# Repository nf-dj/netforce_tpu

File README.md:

Netforce TPU
============

Building hardware to run transformer neural networks at low cost.

Join the [Discord server](https://discord.gg/e4aWKnZZ) for questions and discussions.

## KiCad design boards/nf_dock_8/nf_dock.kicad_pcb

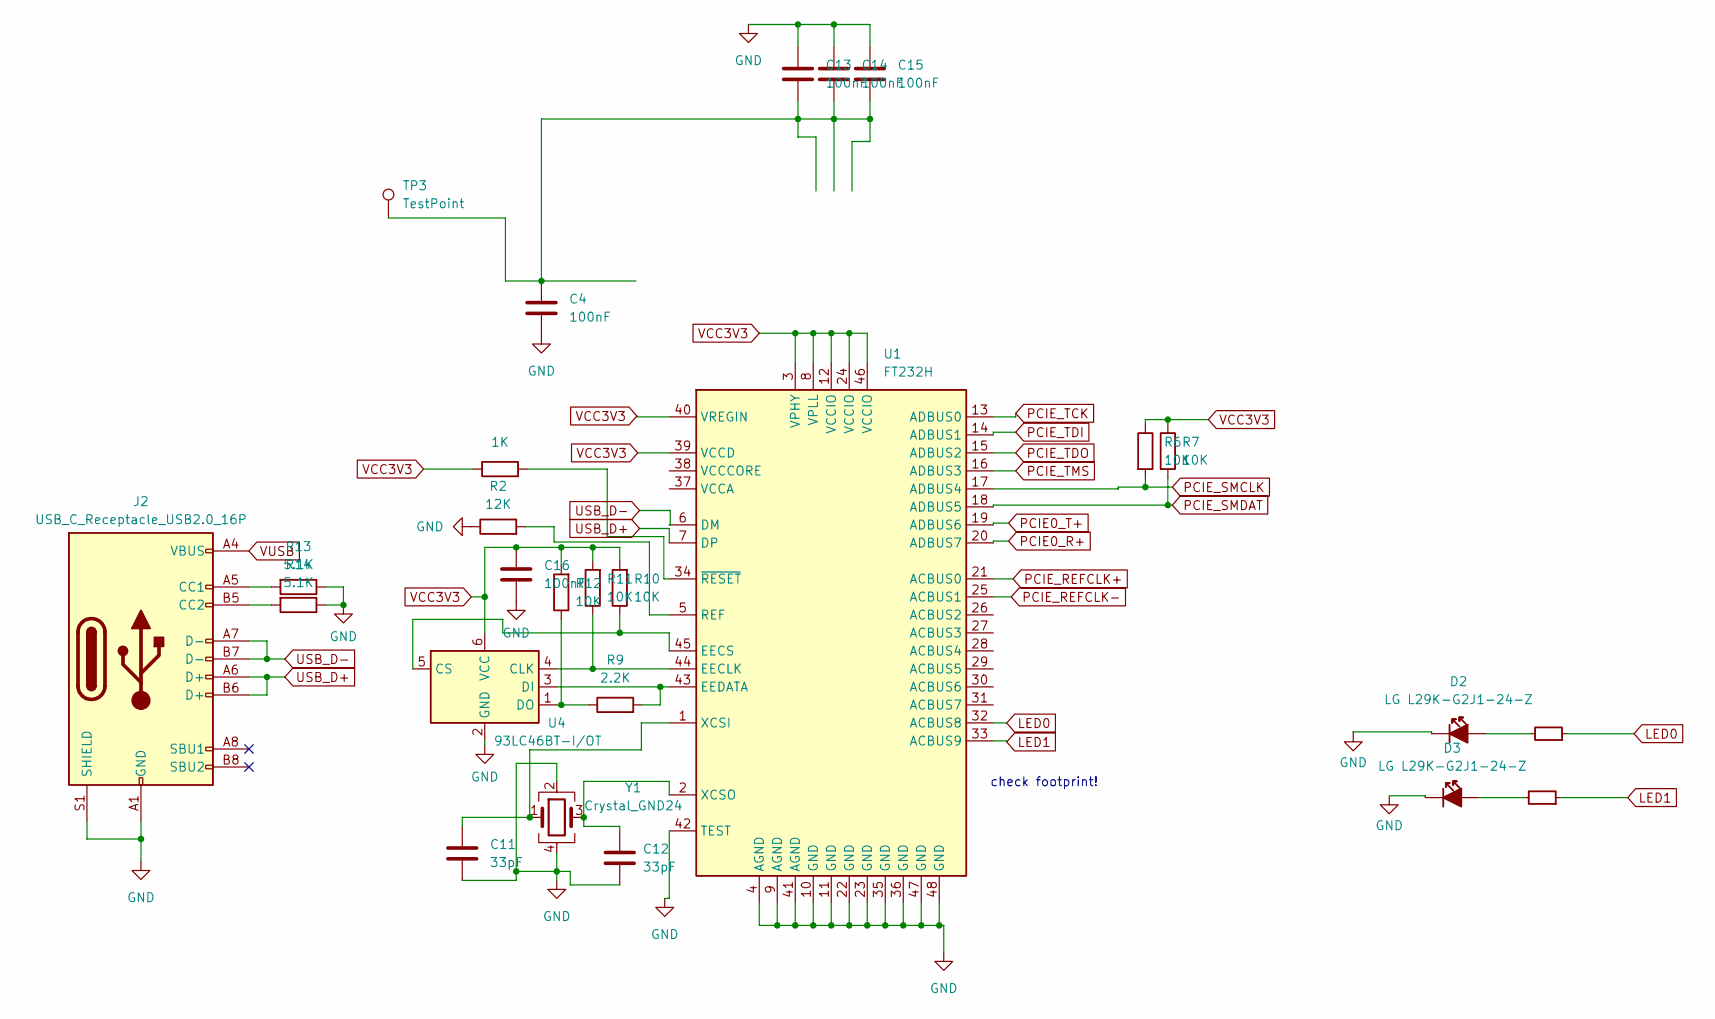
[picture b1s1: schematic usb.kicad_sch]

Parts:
C4, C13, C14, C15, C16: 100nF; C_0402_1005Metric; LCSC C1525
C11, C12: 33pF; C_0402_1005Metric; LCSC C1562
D2: LED_G_0603_LG_L29K-G2J1-24-Z; LED_0805_2012Metric; MPN LG L29K-G2J1-24-Z; LCSC C2297
D3: LED_G_0603_LG_L29K-G2J1-24-Z; LED_0805_2012Metric; MPN LG L29K-G2J1-24-Z; LCSC C84256
J2: USB_C_Receptacle_USB2.0_16P; USB_C_Receptacle_XKB_U262-16XN-4BVC11; LCSC C165948
R2: 12K; R_0402_1005Metric; LCSC C25752
R6, R7, R10, R11, R12: 10K; R_0402_1005Metric; LCSC C25744
R8: 1K; R_0402_1005Metric; LCSC C11702
R9: 2.2K; R_0402_1005Metric; LCSC C25879
R13, R14: 5.1K; R_0402_1005Metric; LCSC C25905
R16, R17: 330R; R_0402_1005Metric; Tolerance 1%; MPN CR0402-FX-1001GLF; LCSC C25104
TP3: TestPoint; TestPoint_Pad_D1.0mm
U1: FT232H; QFN-48-1EP_7x7mm_P0.5mm_EP3.5x3.5mm; LCSC C51997
U4: 93LC46BT-I/OT; SOT-23-6; LCSC C190271
Y1: Crystal_GND24; Crystal_SMD_3225-4Pin_3.2x2.5mm; LCSC C9002

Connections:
GND: C4.2, C11.2, C12.2, C13.1, C14.1, C15.1, C16.2, D2.2, D3.2, J2.A1 (GND), J2.A12 (GND), J2.B1 (GND), J2.B12 (GND), J2.S1 (SHIELD), R2.1, R13.1, R14.1, U1.4 (AGND), U1.9 (AGND), U1.10 (GND), U1.11 (GND), U1.22 (GND), U1.23 (GND), U1.35 (GND), U1.36 (GND), U1.42 (TEST), U1.47 (GND), U1.48 (GND), U4.2 (GND), Y1.2, Y1.4; also elsewhere on the board
LED0: R17.1, U1.32 (ACBUS8)
LED1: R16.1, U1.33 (ACBUS9)
unnamed: C4.1, C13.2, C14.2, C15.2, TP3.1
unnamed: D2.1, R17.2
unnamed: D3.1, R16.2
unnamed: J2.A5 (CC1), R13.2
unnamed: J2.B5 (CC2), R14.2
unnamed: R11.1, U1.44 (EECLK), U4.4 (CLK)
unnamed: R10.1, U1.45 (EECS), U4.5 (CS)
unnamed: R9.2, U1.43 (EEDATA), U4.3 (DI)
unnamed: R2.2, U1.5 (REF)
unnamed: C11.1, U1.1 (XCSI), Y1.1
unnamed: C12.1, U1.2 (XCSO), Y1.3
unnamed: R8.2, U1.34 (~RESET)
unnamed: R9.1, R12.1, U4.1 (DO)
PCIE0_R+: U1.20 (ADBUS7); also elsewhere on the board
PCIE0_T+: U1.19 (ADBUS6); also elsewhere on the board
PCIE_REFCLK+: U1.21 (ACBUS0); also elsewhere on the board
PCIE_REFCLK-: U1.25 (ACBUS1); also elsewhere on the board
PCIE_SMCLK: R6.2, U1.17 (ADBUS4); also elsewhere on the board
PCIE_SMDAT: R7.2, U1.18 (ADBUS5); also elsewhere on the board
PCIE_TCK: U1.13 (ADBUS0); also elsewhere on the board
PCIE_TDI: U1.14 (ADBUS1); also elsewhere on the board
PCIE_TDO: U1.15 (ADBUS2); also elsewhere on the board
PCIE_TMS: U1.16 (ADBUS3); also elsewhere on the board
USB_D+: J2.A6 (D+), J2.B6 (D+), U1.7 (DP)
USB_D-: J2.A7 (D-), J2.B7 (D-), U1.6 (DM)
VCC3V3: C16.1, R6.1, R7.1, R8.1, R10.2, R11.2, R12.2, U1.3 (VPHY), U1.8 (VPLL), U1.12 (VCCIO), U1.24 (VCCIO), U1.39 (VCCD), U1.40 (VREGIN), U1.46 (VCCIO), U4.6 (VCC); also elsewhere on the board
VUSB: J2.A4 (VBUS), J2.A9 (VBUS), J2.B4 (VBUS), J2.B9 (VBUS); also elsewhere on the board

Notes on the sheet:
check footprint!

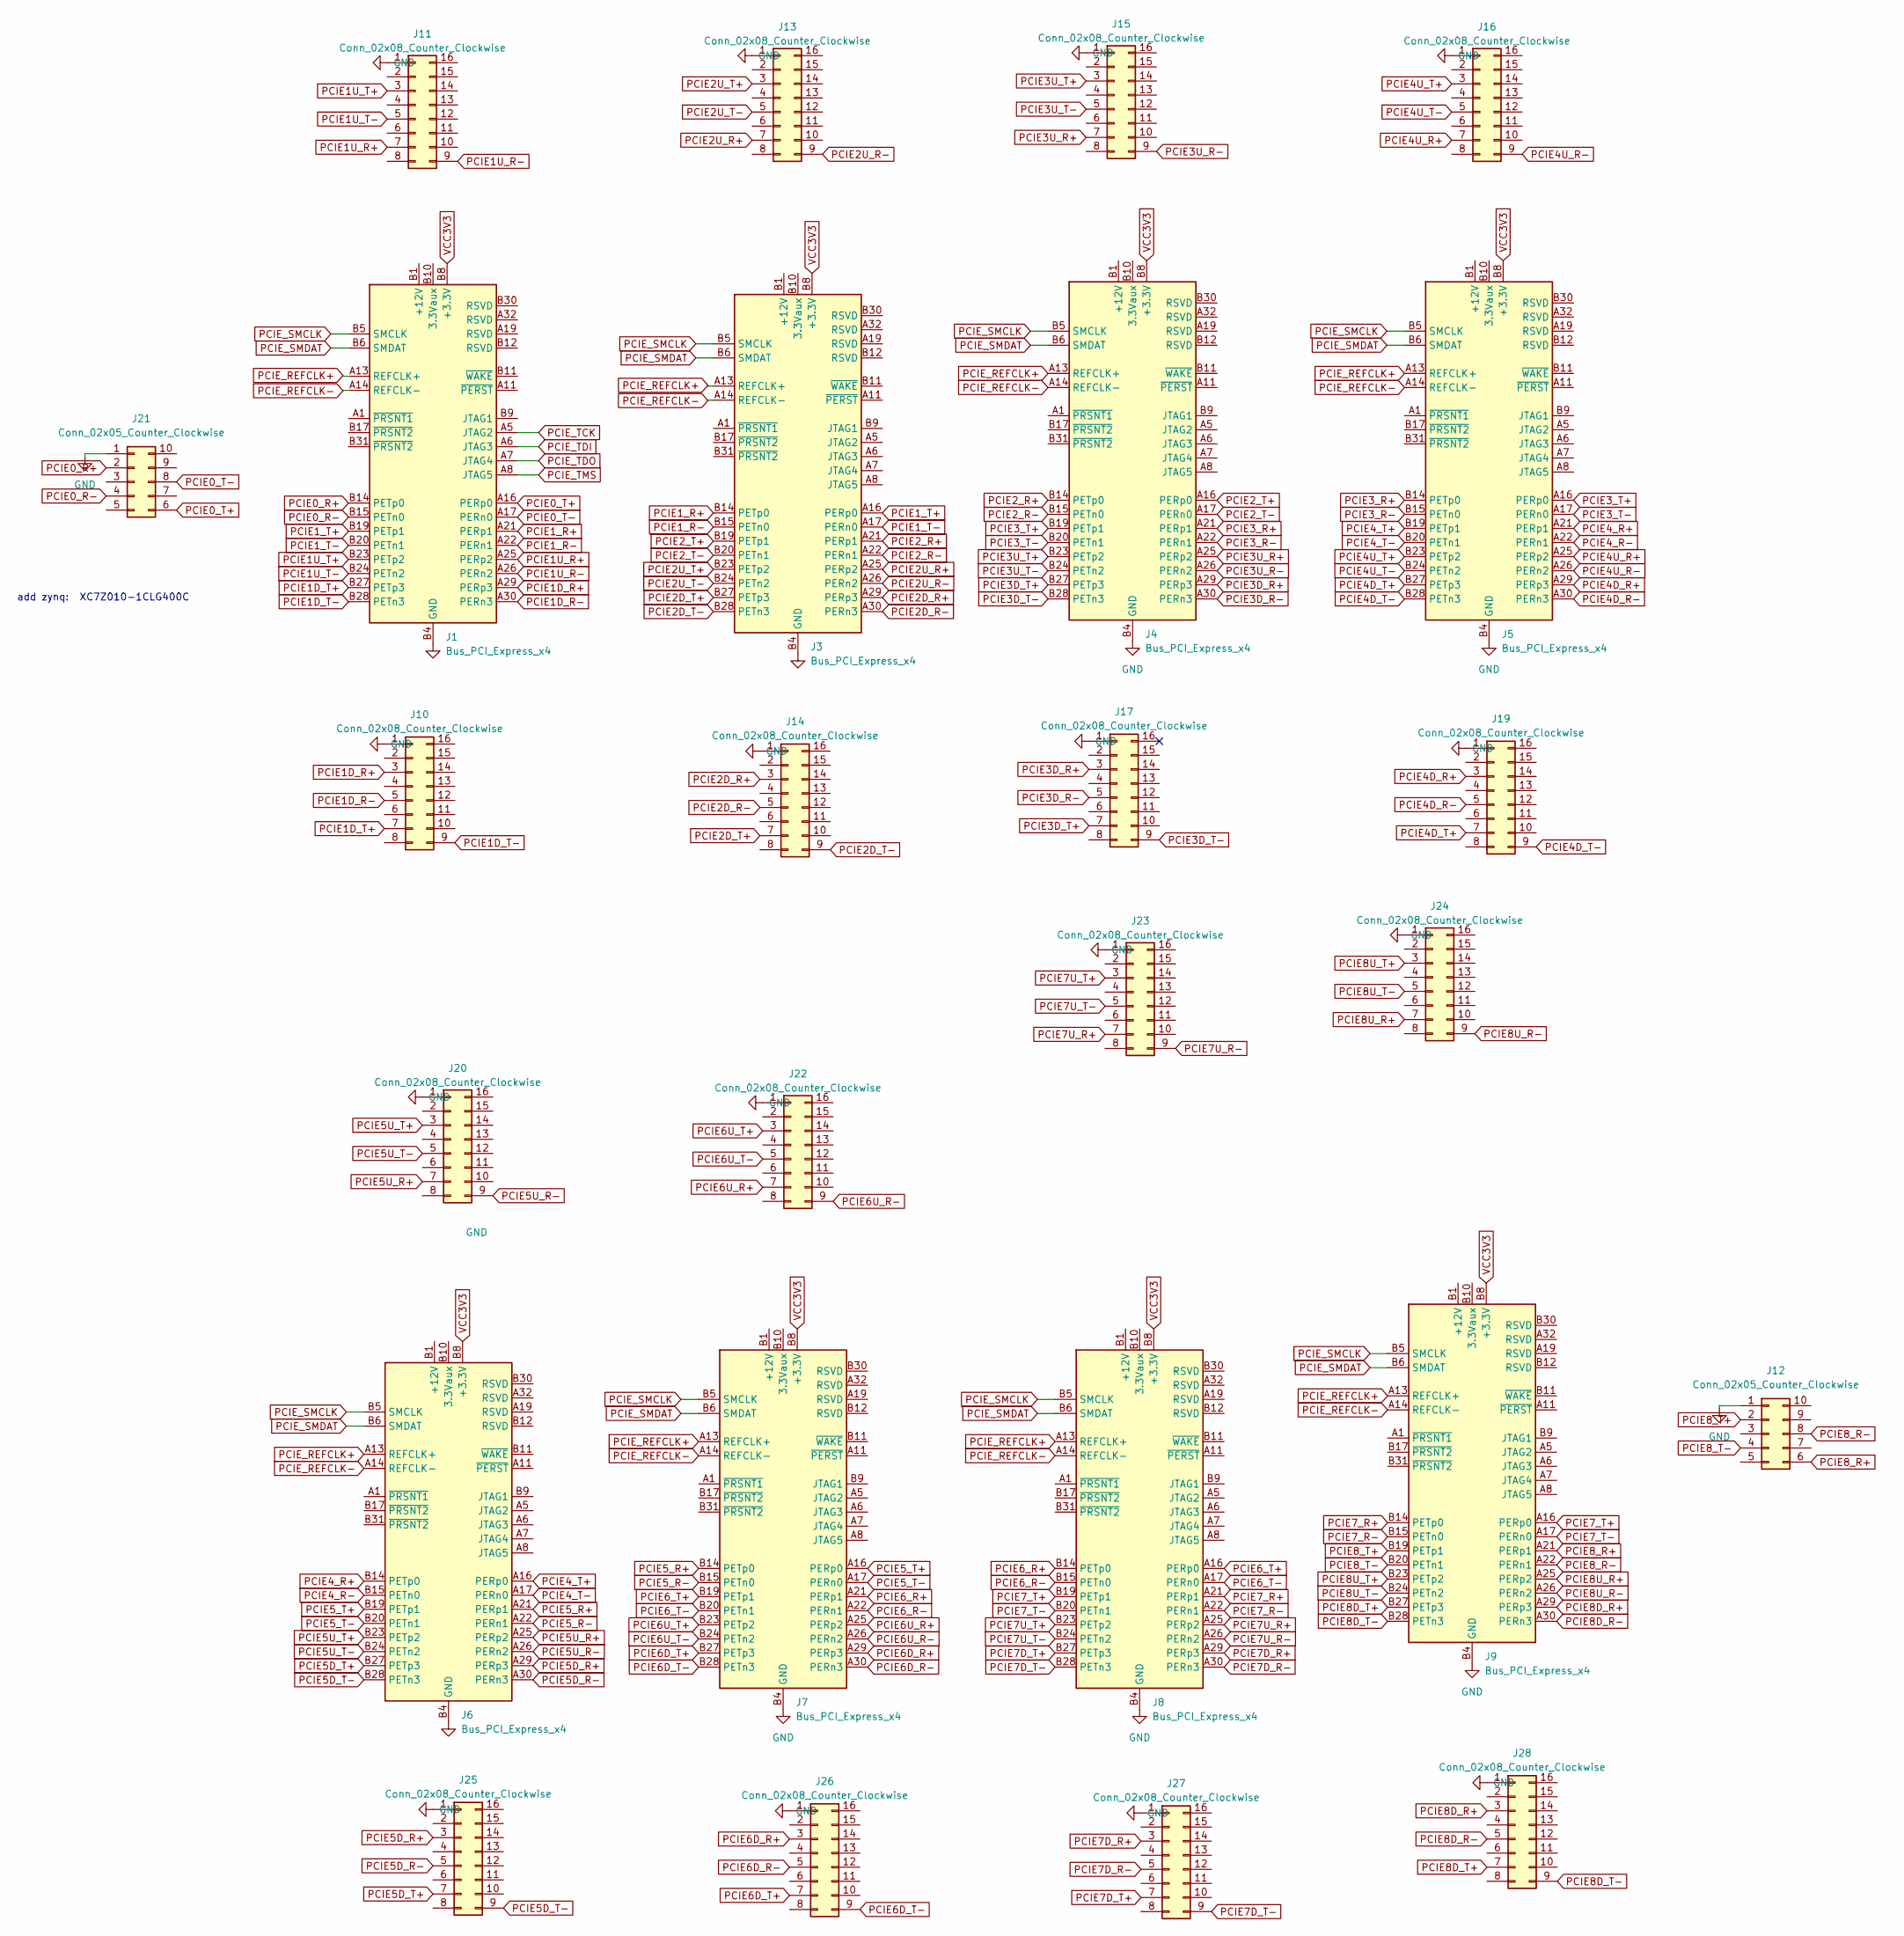
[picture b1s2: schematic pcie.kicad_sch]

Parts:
J1, J3, J4, J5, J6, J7, J8, J9: Bus_PCI_Express_x4; pcie-x4-slot; LCSC C404102
J10, J14, J17, J19, J25, J26, J27, J28: Conn_02x08_Counter_Clockwise; PinSocket_2x08_P1.27mm_Horizontal
J11, J13, J15, J16, J20, J22, J23, J24: Conn_02x08_Counter_Clockwise; PinHeader_2x08_P1.27mm_Horizontal; LCSC C2881828
J12, J21: Conn_02x05_Counter_Clockwise; IDC-Header_2x05_P2.54mm_Vertical

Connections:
GND: J1.A4 (GND), J1.A12 (GND), J1.A15 (GND), J1.A18 (GND), J1.A20 (GND), J1.A23 (GND), J1.A24 (GND), J1.A27 (GND), J1.A28 (GND), J1.A31 (GND), J1.B4 (GND), J1.B7 (GND), J1.B13 (GND), J1.B16 (GND), J1.B18 (GND), J1.B21 (GND), J1.B22 (GND), J1.B25 (GND), J1.B26 (GND), J1.B29 (GND), J1.B32 (GND), J3.A4 (GND), J3.A12 (GND), J3.A15 (GND), J3.A18 (GND), J3.A20 (GND), J3.A23 (GND), J3.A24 (GND), J3.A27 (GND), J3.A28 (GND), J3.A31 (GND), J3.B4 (GND), J3.B7 (GND), J3.B13 (GND), J3.B16 (GND), J3.B18 (GND), J3.B21 (GND), J3.B22 (GND), J3.B25 (GND), J3.B26 (GND), J3.B29 (GND), J3.B32 (GND), J4.A4 (GND), J4.A12 (GND), J4.A15 (GND), J4.A18 (GND), J4.A20 (GND), J4.A23 (GND), J4.A24 (GND), J4.A27 (GND), J4.A28 (GND), J4.A31 (GND), J4.B4 (GND), J4.B7 (GND), J4.B13 (GND), J4.B16 (GND), J4.B18 (GND), J4.B21 (GND), J4.B22 (GND), J4.B25 (GND), J4.B26 (GND), J4.B29 (GND), J4.B32 (GND), J5.A4 (GND), J5.A12 (GND), J5.A15 (GND), J5.A18 (GND), J5.A20 (GND), J5.A23 (GND), J5.A24 (GND), J5.A27 (GND), J5.A28 (GND), J5.A31 (GND), J5.B4 (GND), J5.B7 (GND), J5.B13 (GND), J5.B16 (GND), J5.B18 (GND), J5.B21 (GND), J5.B22 (GND), J5.B25 (GND), J5.B26 (GND), J5.B29 (GND), J5.B32 (GND), J6.A4 (GND), J6.A12 (GND), J6.A15 (GND), J6.A18 (GND), J6.A20 (GND), J6.A23 (GND), J6.A24 (GND), J6.A27 (GND), J6.A28 (GND), J6.A31 (GND), J6.B4 (GND), J6.B7 (GND), J6.B13 (GND), J6.B16 (GND), J6.B18 (GND), J6.B21 (GND), J6.B22 (GND), J6.B25 (GND), J6.B26 (GND), J6.B29 (GND), J6.B32 (GND), J7.A4 (GND), J7.A12 (GND), J7.A15 (GND), J7.A18 (GND), J7.A20 (GND), J7.A23 (GND), J7.A24 (GND), J7.A27 (GND), J7.A28 (GND), J7.A31 (GND), J7.B4 (GND), J7.B7 (GND), J7.B13 (GND), J7.B16 (GND), J7.B18 (GND), J7.B21 (GND), J7.B22 (GND), J7.B25 (GND), J7.B26 (GND), J7.B29 (GND), J7.B32 (GND), J8.A4 (GND), J8.A12 (GND), J8.A15 (GND), J8.A18 (GND), J8.A20 (GND), J8.A23 (GND), J8.A24 (GND), J8.A27 (GND), J8.A28 (GND), J8.A31 (GND), J8.B4 (GND), J8.B7 (GND), J8.B13 (GND), J8.B16 (GND), J8.B18 (GND), J8.B21 (GND), J8.B22 (GND), J8.B25 (GND), J8.B26 (GND), J8.B29 (GND), J8.B32 (GND), J9.A4 (GND), J9.A12 (GND), J9.A15 (GND), J9.A18 (GND), J9.A20 (GND), J9.A23 (GND), J9.A24 (GND), J9.A27 (GND), J9.A28 (GND), J9.A31 (GND), J9.B4 (GND), J9.B7 (GND), J9.B13 (GND), J9.B16 (GND), J9.B18 (GND), J9.B21 (GND), J9.B22 (GND), J9.B25 (GND), J9.B26 (GND), J9.B29 (GND), J9.B32 (GND), J10.1, J11.1, J12.1, J13.1, J14.1, J15.1, J16.1, J17.1, J19.1, J20.1, J21.1, J22.1, J23.1, J24.1, J25.1, J26.1, J27.1, J28.1; also elsewhere on the board
unnamed: J1.A2 (+12V), J1.A3 (+12V), J1.B1 (+12V), J1.B2 (+12V), J1.B3 (+12V)
unnamed: J3.A2 (+12V), J3.A3 (+12V), J3.B1 (+12V), J3.B2 (+12V), J3.B3 (+12V)
unnamed: J4.A2 (+12V), J4.A3 (+12V), J4.B1 (+12V), J4.B2 (+12V), J4.B3 (+12V)
unnamed: J5.A2 (+12V), J5.A3 (+12V), J5.B1 (+12V), J5.B2 (+12V), J5.B3 (+12V)
unnamed: J6.A2 (+12V), J6.A3 (+12V), J6.B1 (+12V), J6.B2 (+12V), J6.B3 (+12V)
unnamed: J7.A2 (+12V), J7.A3 (+12V), J7.B1 (+12V), J7.B2 (+12V), J7.B3 (+12V)
unnamed: J8.A2 (+12V), J8.A3 (+12V), J8.B1 (+12V), J8.B2 (+12V), J8.B3 (+12V)
unnamed: J9.A2 (+12V), J9.A3 (+12V), J9.B1 (+12V), J9.B2 (+12V), J9.B3 (+12V)
PCIE0_R+: J1.B14 (PETp0), J21.2; also elsewhere on the board
PCIE0_R-: J1.B15 (PETn0), J21.4
PCIE0_T+: J1.A16 (PERp0), J21.6; also elsewhere on the board
PCIE0_T-: J1.A17 (PERn0), J21.8
PCIE1D_R+: J1.A29 (PERp3), J10.3
PCIE1D_R-: J1.A30 (PERn3), J10.5
PCIE1D_T+: J1.B27 (PETp3), J10.7
PCIE1D_T-: J1.B28 (PETn3), J10.9
PCIE1U_R+: J1.A25 (PERp2), J11.7
PCIE1U_R-: J1.A26 (PERn2), J11.9
PCIE1U_T+: J1.B23 (PETp2), J11.3
PCIE1U_T-: J1.B24 (PETn2), J11.5
PCIE1_R+: J1.A21 (PERp1), J3.B14 (PETp0)
PCIE1_R-: J1.A22 (PERn1), J3.B15 (PETn0)
PCIE1_T+: J1.B19 (PETp1), J3.A16 (PERp0)
PCIE1_T-: J1.B20 (PETn1), J3.A17 (PERn0)
PCIE2D_R+: J3.A29 (PERp3), J14.3
PCIE2D_R-: J3.A30 (PERn3), J14.5
PCIE2D_T+: J3.B27 (PETp3), J14.7
PCIE2D_T-: J3.B28 (PETn3), J14.9
PCIE2U_R+: J3.A25 (PERp2), J13.7
PCIE2U_R-: J3.A26 (PERn2), J13.9
PCIE2U_T+: J3.B23 (PETp2), J13.3
PCIE2U_T-: J3.B24 (PETn2), J13.5
PCIE2_R+: J3.A21 (PERp1), J4.B14 (PETp0)
PCIE2_R-: J3.A22 (PERn1), J4.B15 (PETn0)
PCIE2_T+: J3.B19 (PETp1), J4.A16 (PERp0)
PCIE2_T-: J3.B20 (PETn1), J4.A17 (PERn0)
PCIE3D_R+: J4.A29 (PERp3), J17.3
PCIE3D_R-: J4.A30 (PERn3), J17.5
PCIE3D_T+: J4.B27 (PETp3), J17.7
PCIE3D_T-: J4.B28 (PETn3), J17.9
PCIE3U_R+: J4.A25 (PERp2), J15.7
PCIE3U_R-: J4.A26 (PERn2), J15.9
PCIE3U_T+: J4.B23 (PETp2), J15.3
PCIE3U_T-: J4.B24 (PETn2), J15.5
PCIE3_R+: J4.A21 (PERp1), J5.B14 (PETp0)
PCIE3_R-: J4.A22 (PERn1), J5.B15 (PETn0)
PCIE3_T+: J4.B19 (PETp1), J5.A16 (PERp0)
PCIE3_T-: J4.B20 (PETn1), J5.A17 (PERn0)
PCIE4D_R+: J5.A29 (PERp3), J19.3
PCIE4D_R-: J5.A30 (PERn3), J19.5
PCIE4D_T+: J5.B27 (PETp3), J19.7
PCIE4D_T-: J5.B28 (PETn3), J19.9
PCIE4U_R+: J5.A25 (PERp2), J16.7
PCIE4U_R-: J5.A26 (PERn2), J16.9
PCIE4U_T+: J5.B23 (PETp2), J16.3
PCIE4U_T-: J5.B24 (PETn2), J16.5
PCIE4_R+: J5.A21 (PERp1), J6.B14 (PETp0)
PCIE4_R-: J5.A22 (PERn1), J6.B15 (PETn0)
PCIE4_T+: J5.B19 (PETp1), J6.A16 (PERp0)
PCIE4_T-: J5.B20 (PETn1), J6.A17 (PERn0)
PCIE5D_R+: J6.A29 (PERp3), J25.3
PCIE5D_R-: J6.A30 (PERn3), J25.5
PCIE5D_T+: J6.B27 (PETp3), J25.7
PCIE5D_T-: J6.B28 (PETn3), J25.9
PCIE5U_R+: J6.A25 (PERp2), J20.7
PCIE5U_R-: J6.A26 (PERn2), J20.9
PCIE5U_T+: J6.B23 (PETp2), J20.3
PCIE5U_T-: J6.B24 (PETn2), J20.5
PCIE5_R+: J6.A21 (PERp1), J7.B14 (PETp0)
PCIE5_R-: J6.A22 (PERn1), J7.B15 (PETn0)
PCIE5_T+: J6.B19 (PETp1), J7.A16 (PERp0)
PCIE5_T-: J6.B20 (PETn1), J7.A17 (PERn0)
PCIE6D_R+: J7.A29 (PERp3), J26.3
PCIE6D_R-: J7.A30 (PERn3), J26.5
PCIE6D_T+: J7.B27 (PETp3), J26.7
PCIE6D_T-: J7.B28 (PETn3), J26.9
PCIE6U_R+: J7.A25 (PERp2), J22.7
PCIE6U_R-: J7.A26 (PERn2), J22.9
PCIE6U_T+: J7.B23 (PETp2), J22.3
PCIE6U_T-: J7.B24 (PETn2), J22.5
PCIE6_R+: J7.A21 (PERp1), J8.B14 (PETp0)
PCIE6_R-: J7.A22 (PERn1), J8.B15 (PETn0)
PCIE6_T+: J7.B19 (PETp1), J8.A16 (PERp0)
PCIE6_T-: J7.B20 (PETn1), J8.A17 (PERn0)
PCIE7D_R+: J8.A29 (PERp3), J27.3
PCIE7D_R-: J8.A30 (PERn3), J27.5
PCIE7D_T+: J8.B27 (PETp3), J27.7
PCIE7D_T-: J8.B28 (PETn3), J27.9
PCIE7U_R+: J8.A25 (PERp2), J23.7
PCIE7U_R-: J8.A26 (PERn2), J23.9
PCIE7U_T+: J8.B23 (PETp2), J23.3
PCIE7U_T-: J8.B24 (PETn2), J23.5
PCIE7_R+: J8.A21 (PERp1), J9.B14 (PETp0)
PCIE7_R-: J8.A22 (PERn1), J9.B15 (PETn0)
PCIE7_T+: J8.B19 (PETp1), J9.A16 (PERp0)
PCIE7_T-: J8.B20 (PETn1), J9.A17 (PERn0)
PCIE8D_R+: J9.A29 (PERp3), J28.3
PCIE8D_R-: J9.A30 (PERn3), J28.5
PCIE8D_T+: J9.B27 (PETp3), J28.7
PCIE8D_T-: J9.B28 (PETn3), J28.9
PCIE8U_R+: J9.A25 (PERp2), J24.7
PCIE8U_R-: J9.A26 (PERn2), J24.9
PCIE8U_T+: J9.B23 (PETp2), J24.3
PCIE8U_T-: J9.B24 (PETn2), J24.5
PCIE8_R+: J9.A21 (PERp1), J12.6
PCIE8_R-: J9.A22 (PERn1), J12.8
PCIE8_T+: J9.B19 (PETp1), J12.2
PCIE8_T-: J9.B20 (PETn1), J12.4
PCIE_REFCLK+: J1.A13 (REFCLK+), J3.A13 (REFCLK+), J4.A13 (REFCLK+), J5.A13 (REFCLK+), J6.A13 (REFCLK+), J7.A13 (REFCLK+), J8.A13 (REFCLK+), J9.A13 (REFCLK+); also elsewhere on the board
PCIE_REFCLK-: J1.A14 (REFCLK-), J3.A14 (REFCLK-), J4.A14 (REFCLK-), J5.A14 (REFCLK-), J6.A14 (REFCLK-), J7.A14 (REFCLK-), J8.A14 (REFCLK-), J9.A14 (REFCLK-); also elsewhere on the board
PCIE_SMCLK: J1.B5 (SMCLK), J3.B5 (SMCLK), J4.B5 (SMCLK), J5.B5 (SMCLK), J6.B5 (SMCLK), J7.B5 (SMCLK), J8.B5 (SMCLK), J9.B5 (SMCLK); also elsewhere on the board
PCIE_SMDAT: J1.B6 (SMDAT), J3.B6 (SMDAT), J4.B6 (SMDAT), J5.B6 (SMDAT), J6.B6 (SMDAT), J7.B6 (SMDAT), J8.B6 (SMDAT), J9.B6 (SMDAT); also elsewhere on the board
PCIE_TCK: J1.A5 (JTAG2); also elsewhere on the board
PCIE_TDI: J1.A6 (JTAG3); also elsewhere on the board
PCIE_TDO: J1.A7 (JTAG4); also elsewhere on the board
PCIE_TMS: J1.A8 (JTAG5); also elsewhere on the board
VCC3V3: J1.A9 (+3.3V), J1.A10 (+3.3V), J1.B8 (+3.3V), J3.A9 (+3.3V), J3.A10 (+3.3V), J3.B8 (+3.3V), J4.A9 (+3.3V), J4.A10 (+3.3V), J4.B8 (+3.3V), J5.A9 (+3.3V), J5.A10 (+3.3V), J5.B8 (+3.3V), J6.A9 (+3.3V), J6.A10 (+3.3V), J6.B8 (+3.3V), J7.A9 (+3.3V), J7.A10 (+3.3V), J7.B8 (+3.3V), J8.A9 (+3.3V), J8.A10 (+3.3V), J8.B8 (+3.3V), J9.A9 (+3.3V), J9.A10 (+3.3V), J9.B8 (+3.3V); also elsewhere on the board

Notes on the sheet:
add zynq: XC7Z010-1CLG400C

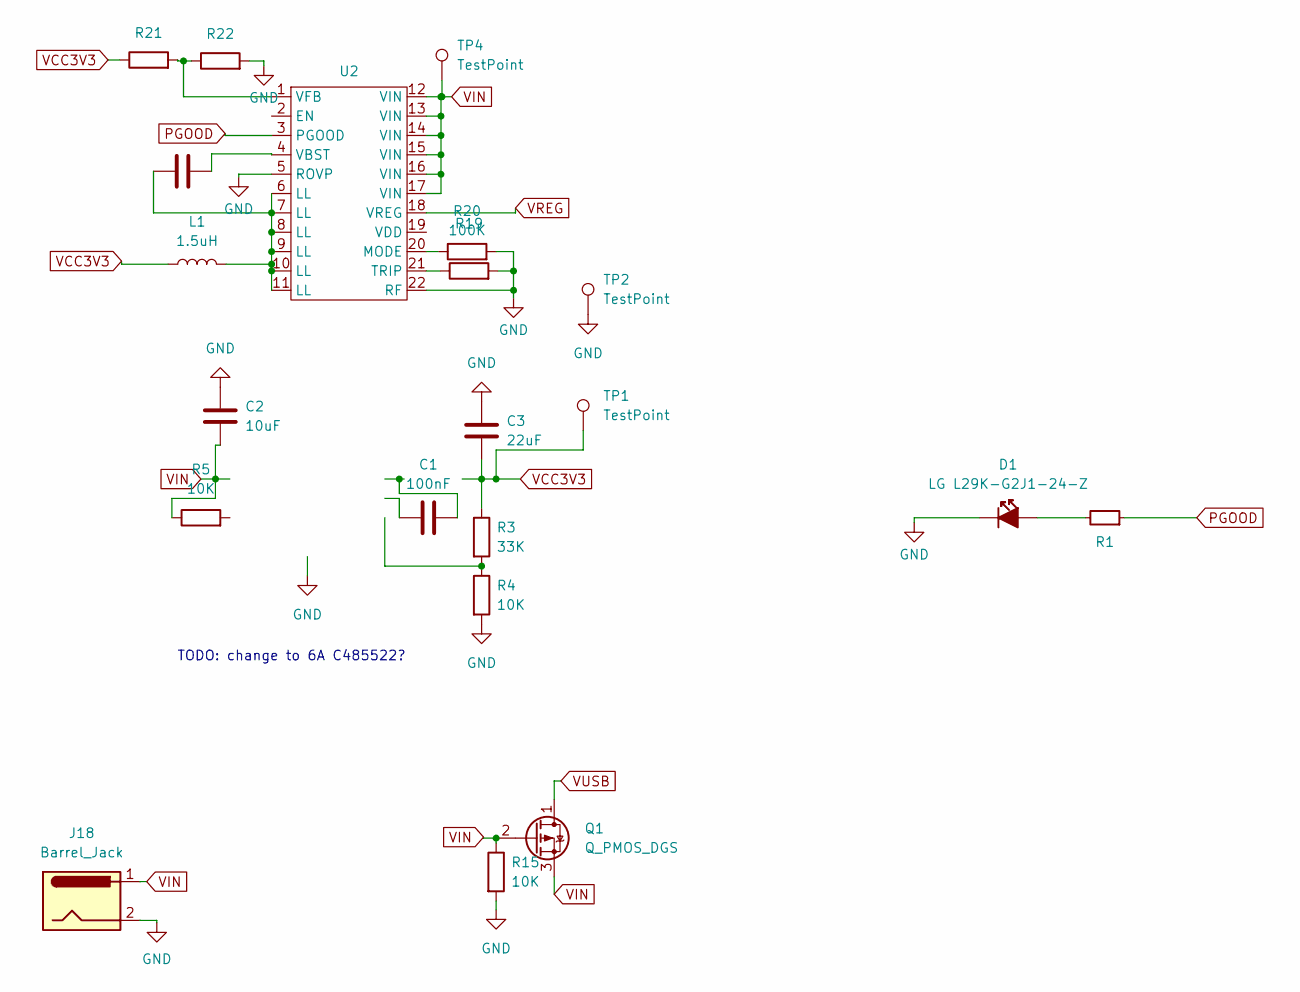
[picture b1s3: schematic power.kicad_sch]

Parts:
C1: 100nF; C_0402_1005Metric; LCSC C1525
C2: 10uF; C_0603_1608Metric; LCSC C19702
C3: 22uF; C_0603_1608Metric; LCSC C59461
C5: C_0402_1005Metric; LCSC C1525
D1: LED_G_0603_LG_L29K-G2J1-24-Z; LED_0805_2012Metric; MPN LG L29K-G2J1-24-Z; LCSC C34499
J18: Barrel_Jack; dc_conn; LCSC C19189083
L1: 1.5uH; pwr_inductor_10040; LCSC C280566
Q1: Q_PMOS_DGS; SOT-23; LCSC C10487
R1: 330R; R_0402_1005Metric; Tolerance 1%; MPN CR0402-FX-1001GLF; LCSC C25104
R3: 33K; R_0402_1005Metric; LCSC C25779
R4, R5, R15: 10K; R_0402_1005Metric; LCSC C25744
R19, R21, R22: R_0402_1005Metric
R20: 100K; R_0402_1005Metric
TP1, TP2, TP4: TestPoint; TestPoint_Pad_D1.0mm
U2: CONV_TPS53318DQPR; LCSC C181971

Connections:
GND: C2.2, C3.2, D1.2, J18.2, R4.2, R15.2, R19.2, R20.2, R22.2, TP2.1, U2.5 (ROVP), U2.22 (RF); also elsewhere on the board
unnamed: C5.1, L1.2, U2.6 (LL), U2.7 (LL), U2.8 (LL), U2.9 (LL), U2.10 (LL), U2.11 (LL)
unnamed: D1.1, R1.2
unnamed: R3.2, R4.1
unnamed: R20.1, U2.20 (MODE)
unnamed: R19.1, U2.21 (TRIP)
unnamed: C5.2, U2.4 (VBST)
unnamed: R21.2, R22.1, U2.1 (VFB)
PGOOD: R1.1, U2.3 (PGOOD)
VCC3V3: C3.1, L1.1, R3.1, R21.1, TP1.1; also elsewhere on the board
VIN: C2.1, J18.1, Q1.2 (G), Q1.3 (S), R5.1, R15.1, TP4.1, U2.12 (VIN), U2.13 (VIN), U2.14 (VIN), U2.15 (VIN), U2.16 (VIN), U2.17 (VIN)
VREG: U2.18 (VREG)
VUSB: Q1.1 (D); also elsewhere on the board

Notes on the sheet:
TODO: change to 6A C485522?

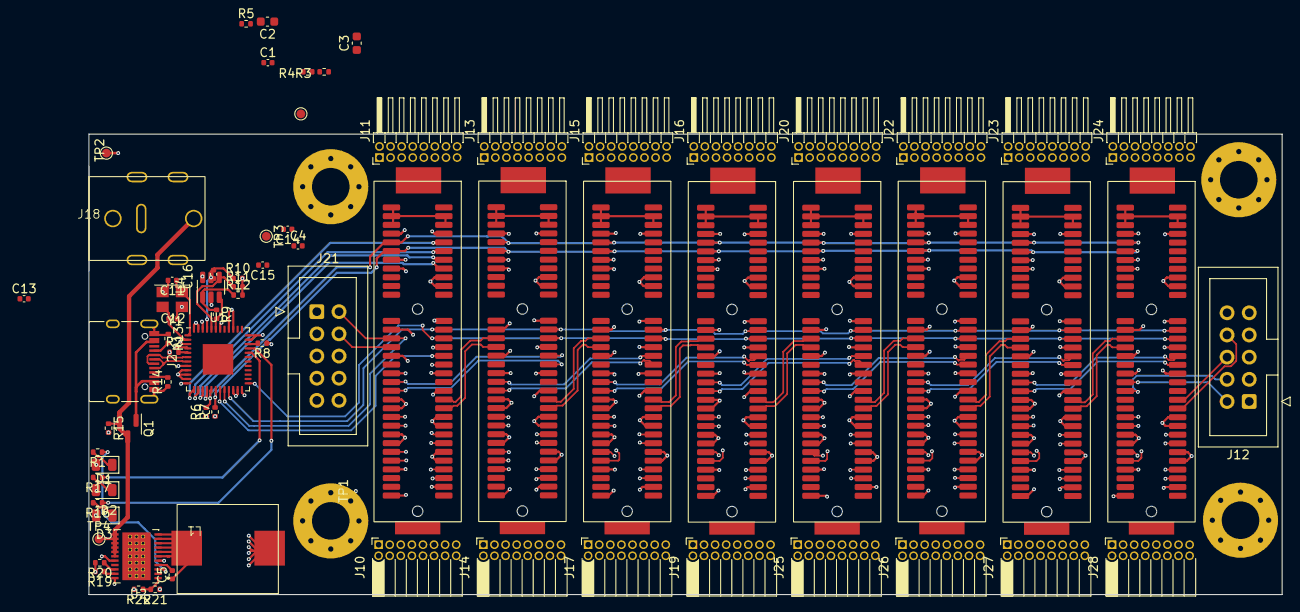
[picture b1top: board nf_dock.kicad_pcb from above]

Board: 4 copper layers, 136.7 x 52.7 mm, 77 parts (0 on the bottom side), 145 nets.

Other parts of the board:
H4, H4#2, H4#3, H4#4: MountingHole; MountingHole_4.3mm_M4_Pad_Via

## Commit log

2024-09-02 first
2024-09-02 readme
2024-09-03 artix board
2024-09-03 ecp5 board
2024-09-03 add discord
2024-09-03 add dock
2024-09-03 schematic
2024-09-03 rename
2024-09-04 test led
2024-09-04 test
2024-09-05 spinal
2024-09-05 remove spinal first
2024-09-05 migen
2024-09-05 instruction decode
2024-09-07 board
2024-09-07 schem
2024-09-08 tabs
2024-09-10 ecp5 io
2024-09-10 art7 io
2024-09-11 board drc
2024-09-14 switch tile
2024-09-14 dot tile
2024-09-14 vec tile
2024-09-14 retab
2024-09-15 wrapper
2024-09-16 ddr sim
2024-09-16 dram sim
2024-09-16 cache
2024-09-17 fp8 test
2024-09-17 fp8_add test
2024-09-17 remove fp8 denormalized numbers
2024-09-17 test fp8
2024-09-18 fp8 mul
2024-09-18 fp8 fma test
2024-09-18 test fp8 fma
2024-09-18 pipelined adder
2024-09-18 pipe
2024-09-18 remove while loop in adder
2024-09-18 synth test
2024-09-18 fp4 test
2024-09-19 bitnet
2024-09-19 remove fp8,bitnet, keep only fp4 int fma
2024-09-19 tests
2024-09-19 fix fma
2024-09-19 add relu
2024-09-19 remove bitnet
2024-09-20 dot block
2024-09-20 slice ins width 64->16
2024-09-20 sw slice
2024-09-20 mem tile
2024-09-20 bram synth
2024-09-20 mem slice
2024-09-20 bidir memtile
2024-09-20 fix id
2024-09-21 switch
2024-09-21 sw tile
2024-09-22 stream io
2024-09-22 dram io
2024-09-22 render sim
2024-09-22 fix link
2024-09-23 add reset
2024-09-23 reset
2024-09-24 sky130 test

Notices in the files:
parts and their libraries:
License: Apache-2.0
